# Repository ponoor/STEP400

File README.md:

# STEP400

STEP400 is a 4-axis stepper motor driver board with an Ethernet interface, designed for art installations, stage productions and exhibition machinery. It puts everything a typical motion setup needs onto one board:

- An Arduino Zero–compatible MCU (Microchip ATSAMD21G18A)
- Ethernet (WIZnet W5500)
- Four [STMicroelectronics powerSTEP01](https://www.st.com/en/motor-drivers/powerstep01.html) stepper drivers, supporting both voltage mode and current mode
- HOME and LIMIT sensor inputs for each axis
- A microSD card slot for loading the configuration file

The board is controlled with [Open Sound Control](https://opensoundcontrol.stanford.edu/) (OSC) over Ethernet, which works natively in Max, TouchDesigner, Processing, openFrameworks, Unity and other creative coding environments.

| | |
|---|---|
| Motor type | Bipolar stepper |
| Supply voltage | 12–72 V (absolute max. 80 V) |
| Max. phase current | 5 A |
| Microstepping | Up to 1/128 |
| PCB size | 120 × 84 mm |

STEP400 is part of the STEP series. Its sibling, [STEP800](https://github.com/ponoor/STEP800), drives eight smaller motors with L6470 drivers and shares the same firmware and OSC commands.

Friend of STEP400 : [STEP800](https://github.com/ponoor/STEP800)

## Store
https://ponoor.com/en/shop/

## Documentation
https://ponoor.com/en/docs/step-series/

Forum: https://github.com/ponoor/step-series-support/discussions

- **[STEP400/STEP800 documentation](https://ponoor.com/en/docs/step-series/)** ([日本語](https://ponoor.com/docs/step-series/))
  - [Tutorial](https://ponoor.com/en/docs/step-series/tutorial/)
  - [OSC command reference](https://ponoor.com/en/docs/step-series/osc-command-reference/)
  - [Hardware details](https://ponoor.com/en/docs/step-series/technical-information/hardware-step400/)
- [Electromagnetic brake board for STEP400](https://ponoor.com/en/docs/emb-step400/)
- Questions and support: [STEP series support forum](https://github.com/ponoor/step-series-support/discussions)

## Firmware

The firmware is maintained in a separate repository, shared with STEP800:

**[ponoor/step-series-universal-firmware](https://github.com/ponoor/step-series-universal-firmware)**

This repository used to contain the STEP400 firmware as well. Those directories have been removed, and the old releases here are no longer maintained. See [Firmware update](https://ponoor.com/en/docs/step-series/technical-information/firmware-update/) in the documentation for how to update a board.

## Repository contents

### `hardware/`

Design files for the current hardware revision (r1).

| File | Description |
|---|---|
| `step400_r1.sch`, `step400_r1.brd` | STEP400 r1 schematic and board (Autodesk EAGLE). These are the reference design files for r1. |
| `step400_r1_schematics.pdf` | STEP400 r1 schematic |
| `step400_r1_dimension.pdf` | Board dimensions and mounting holes |
| `step400_r1.0.1_BOM.csv` | Bill of materials for r1.0.1 (current) |
| `step400_r1.0.0_BOM.csv` | Bill of materials for r1.0.0 |
| `brakeBoard.sch`, `brakeBoard.brd` | Electromagnetic brake board (Autodesk EAGLE) |
| `brakeBoard_schematic.pdf`, `brakeBoard_BOM.csv` | Brake board schematic and bill of materials |
| `step400_r1/` | KiCad project imported from the EAGLE r1 files (see below) |

#### KiCad migration (work in progress)

We are moving the hardware design from EAGLE to KiCad for the next revision. `hardware/step400_r1/` holds the r1 design imported into KiCad 10, along with a footprint library (`step400_r1.pretty`) exported from the board.

The connectivity and footprints of this KiCad project have been checked against the EAGLE files. However, it is kept as a **reference for future work**, not as manufacturing data. The PCB still carries leftovers from the import (an unconsolidated layer stack, missing keepout areas, default design rules), so use the EAGLE files or the PDFs above if you need the exact r1 design.

### `configTool/`

Source of the web-based configuration tool, which creates the JSON configuration file that the board loads from its microSD card. A hosted version is available at [ponoor.com/tools/step400-config/](https://ponoor.com/tools/step400-config/). For usage, see [Setup with a microSD card](https://ponoor.com/en/docs/step-series/settings/setup-with-a-microsd-card/).

### `step400_hardware_tests/`

A PlatformIO project for the hardware inspection firmware, used to test assembled boards.

## Examples and libraries

| Environment | Repository |
|---|---|
| Max | [ponoor/step-series-example-Max](https://github.com/ponoor/step-series-example-Max) |
| TouchDesigner | [ponoor/step-series-example-TouchDesigner](https://github.com/ponoor/step-series-example-TouchDesigner) (by [@loveandsheep](https://github.com/loveandsheep)) |
| openFrameworks | [ponoor/step-series-example-openFrameworks](https://github.com/ponoor/step-series-example-openFrameworks) (by [@niimi](https://github.com/niimi)) |
| Unity | [ponoor/step-series-example-Unity](https://github.com/ponoor/step-series-example-Unity) (by [@niimi](https://github.com/niimi)) |
| Processing | [yuskegoto/STEP400_Processing](https://github.com/yuskegoto/STEP400_Processing) (by [@yuskegoto](https://github.com/yuskegoto)) |
| Node-RED | [yuskegoto/STEP400_Node-RED](https://github.com/yuskegoto/STEP400_Node-RED) (by [@yuskegoto](https://github.com/yuskegoto)) |
| Python | [ponoor/python-step-series](https://github.com/ponoor/python-step-series) |

## License

[MIT License](LICENSE) © Ponoor Experiments Inc.

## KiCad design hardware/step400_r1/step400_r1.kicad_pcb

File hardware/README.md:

# Diagram
```mermaid
flowchart LR
	MCU ---|SPI/SERCOM4| W5500 --- Ethernet
	MCU --- |SPI/SERCOM3|PowerSTEP01 --> Motor
	HomeSw -->|SW| PowerSTEP01
	LimitSw -->|ADCIN| PowerSTEP01
	DIPSW --> MCU
	MCU --> Brake
  ```
  
  Check the [document](https://ponoor.com/en/docs/step-series/technical-information/hardware-step400/) for details.

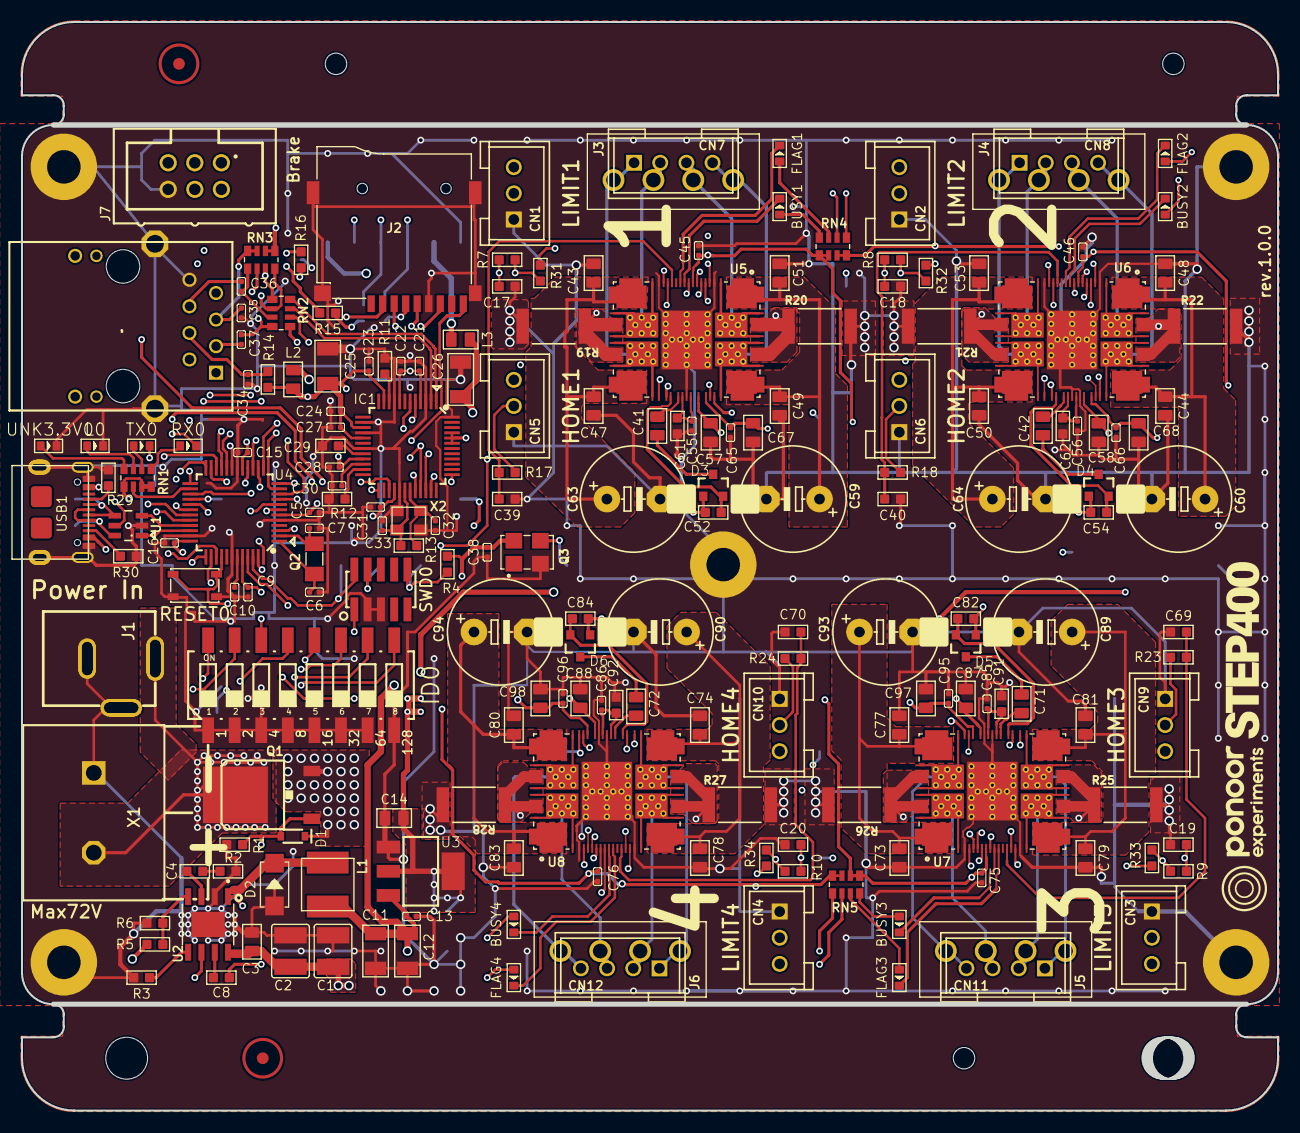
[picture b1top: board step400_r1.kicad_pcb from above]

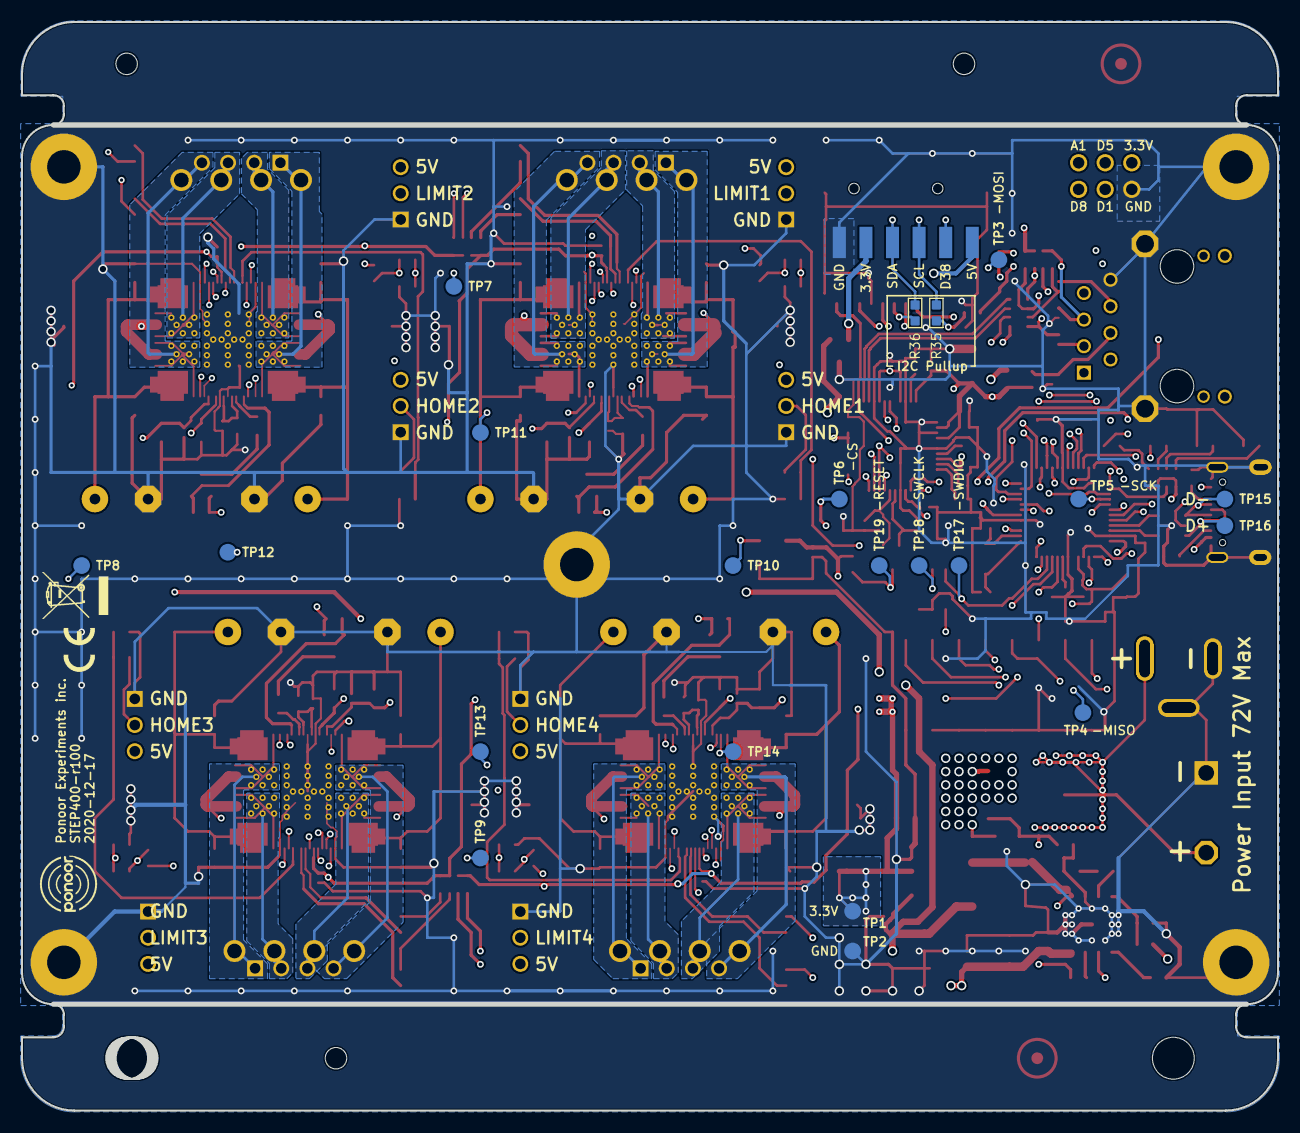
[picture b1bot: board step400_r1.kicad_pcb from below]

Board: 4 copper layers, 120.0 x 104.0 mm, 245 parts (25 on the bottom side), 166 nets.

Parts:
BUSY1, BUSY2, BUSY3, BUSY4: GREEN-0603; LED-0603
C1, C2: 4.7uF/100V; C1210
C3, C57, C58, C87, C88: 100nF/100V; C0805
C4, C8: 100nf; C0603
C5, C9, C10, C13, C15, C16, C21, C22, C23, C24, C27, C28, C31, C38, C45, C46, C55, C56, C75, C76, C85, C86: 100nf; C0402
C6, C7, C32, C33: 22pF; C0402
C11, C12: 47uF; C1206
C14: 10uF/10V; C0805
C17, C18, C19, C20, C39, C40, C69, C70: 1uf; C0603
C25, C26: 47uF/6.3V; C1206
C29: 4.7uF/6.3V; C0603
C30, C35: 10nf; C0402
C34: 22NF 50V; C0402
C36, C37: 6.8nF; C0402
C41, C42, C71, C72: 47nF; C0805
C43, C44, C47, C48, C49, C50, C51, C53, C73, C74, C77, C78, C79, C80, C81, C83: 220nF; C0805
C52, C54, C61, C62, C82, C84, C91, C92: 470nF; C0603
C59, C60, C63, C64, C89, C90, C93, C94: 100uF; E5-10,5
C65, C66, C95, C96: 220nF; C0402
C67, C68, C97, C98: 22uf; C0805
CN1, CN2, CN3, CN4, CN5, CN6, CN9, CN10: B3B-XASK-1
CN7, CN8, CN11, CN12: B4B-XASK-1
D1: 5.1V; SOD-323
D2: 100V 2A; DO-214AC
D3, D4, D5, D6: BAR43; SOT23-3
FLAG1, FLAG2, FLAG3, FLAG4: YELLOW-0603; LED-0603
IC1: 0982_W5500LONG; TQFP48-LONG
ID0: 219-08; CTS-219-08
J1: POWERJACK; POWERJACK_SLOT
J2: SDCARD_SLOT_TF-115K; TF-115K
J3, J4, J5, J6: 691321300004
J7: 61200621621
J8: CONN_06_SMD_FEMALE; 1X06-SMD-FEMALE
L0: BLUE-0603; LED-0603
L1: 150uH; L5045_L
L2, L3: 330R-1500MA; L0805
Q1: SUD50P08-25L-E3; D-PAK_TO252AA
Q2: 32.768kHz; FC-135
Q3: 16MHz; SG5032
R1: 100k; R0603
R2: 4.7k; R0603
R3: 13k; R0603
R4, R12, R31, R32, R33, R34: 10K 1/10W; R0603
R5: 3k; R0603
R6: 750; R0603
R7, R8, R9, R10, R17, R18, R23, R24: 100R; R0603
R11: 12.4K; R0603
R13: 1M 1/10W; R0603
R14: 10R; R0603
R15, R16: 330R; R0603
R19, R20, R21, R22, R25, R26, R27, R28: 0.1; RESC6332X71N
R29, R30: 5.1k; R0603
R35, R36: 4.7K; R0603
RESET0: SWITCH-SPST-2; SKRP
RN1, RN4, RN5: 330; CAY16_LONG_W
RN2: 33; CAY16_LONG_W
RN3: 49.9; CAY16_LONG_W
RX0: RED-0603; LED-0603
S2, S3, S4, S5, S6: STANDOFF_ELECTRICAL; STANDOFF-ELECTRICAL
SWD0: CORTEX_DEBUG_SMT; 20021121-00010C4LF
TP1, TP2, TP3, TP4, TP5, TP6, TP7, TP8, TP9, TP10, TP11, TP12, TP13, TP14, TP15, TP16, TP17, TP18, TP19: TESTPOINT_D1.6
TX0: YELLOW-0603; LED-0603
U1: USBLC6-2SC6; SOT23-6L
U2: BD9G341AEFJ; SOIC127P600X100-9N
U3: LD1117S33; SOT223
U4: ATSAMD21G-A; TQFP-48
U5, U6, U7, U8: POWERSTEP01_VIA; IC_POWERSTEP01_VIA
U$1: STEP400_LOGO_6MM
U$2, U$3: FIDUCIAL_MARKER_PBAN
U$4: PONOOR_LOGO_6MM
U$6: WEEE_6MM
U$8: CE_3MM
UNK3.3V0: GREEN-0603; LED-0603
UNK_HOLE_0: dummyfp0
UNK_HOLE_1: dummyfp1
UNK_HOLE_2: dummyfp2
UNK_HOLE_3: dummyfp3
UNK_HOLE_4: dummyfp4
UNK_HOLE_5: dummyfp5
UNK_HOLE_6: dummyfp6
UNK_HOLE_7: dummyfp7
UNK_HOLE_8: dummyfp8
UNK_HOLE_9: dummyfp9
UNK_HOLE_10: dummyfp10
UNK_HOLE_11: dummyfp11
UNK_HOLE_12: dummyfp12
UNK_HOLE_13: dummyfp13
UNK_HOLE_14: dummyfp14
UNK_HOLE_15: dummyfp15
USB1: USB-C_USB2.0-TYPE-C
X1: CONN_02; WJ25C-B-7.62-2P
X2: 25MHz; CRYSTAL-3.2-2.5
X3: RJ45_MAGNETICS_LED_HR871181A; HR871181A

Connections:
1V2O: C30.2, IC1.22
3.3V: C5.1, C9.1, C14.2, C15.1, C16.1, C38.2, J2.4, J7.5, J8.2, L2.1, L3.1, Q3.4, R4.2, R15.2, R16.2, R35.2, R36.2, RN1.5, RN1.7, RN1.8, SWD0.P$1, TP1.1, U3.2, U3.4, U4.6, U4.17, U4.36, U4.44
5V: C11.2, C12.2, C13.1, CN1.3, CN2.3, CN3.3, CN4.3, CN5.3, CN6.3, CN9.3, CN10.3, J8.6, L1.P$2, R5.2, U1.5, U3.3, USB1.A4_B9, USB1.B4_A9
+3V3A: C21.1, C22.1, C23.1, C24.1, C25.1, C27.1, C28.1, IC1.4, IC1.8, IC1.11, IC1.15, IC1.17, IC1.21, L2.2, R14.2, RN3.1, RN3.2
+3V3D: C26.1, C31.2, IC1.28, IC1.43, IC1.44, IC1.45, L3.2
ACT: IC1.27, X3.12
D13: RN1.6, U4.26
D38: J8.5, U4.22
D+: TP16.1, U1.6, USB1.A6, USB1.B6
D-: TP15.1, U1.4, USB1.A7, USB1.B7
DIPSW1: ID0.16, U4.30
DIPSW2: ID0.15, U4.37
DIPSW3: ID0.14, U4.47
DIPSW4: ID0.13, U4.38
DIPSW5: ID0.12, U4.23
DIPSW6: ID0.11, U4.12
DIPSW7: ID0.10, U4.14
DIPSW8: ID0.9, U4.16
EM_1: J7.1, U4.7
EM_2: J7.2, U4.11
EM_3: J7.3, U4.24
EM_4: J7.4, U4.15
GND: C1.2, C2.2, C3.1, C5.2, C6.1, C7.2, C9.2, C10.2, C11.1, C12.1, C13.2, C14.1, C15.2, C16.2, C17.1, C18.1, C19.1, C20.1, C21.2, C22.2, C23.2, C24.2, C25.2, C26.2, C27.2, C28.2, C29.1, C30.1, C31.1, C32.2, C33.2, C34.2, C35.2, C38.1, C39.1, C40.1, C43.1, C44.1, C45.2, C46.2, C47.1, C48.1, C49.1, C50.1, C51.1, C53.1, C55.2, C56.2, C57.1, C58.1, C59.-, C60.-, C61.1, C62.1, C63.-, C64.-, C65.1, C66.1, C67.1, C68.1, C69.1, C70.1, C73.1, C74.1, C75.2, C76.2, C77.1, C78.1, C79.1, C80.1, C81.1, C83.1, C85.2, C86.2, C87.1, C88.1, C89.-, C90.-, C91.1, C92.1, C93.-, C94.-, C95.1, C96.1, C97.1, C98.1, CN1.1, CN2.1, CN3.1, CN4.1, CN5.1, CN6.1, CN9.1, CN10.1, D2.1, IC1.3, IC1.9, IC1.14, IC1.16, IC1.19, IC1.29, IC1.48, ID0.1, ID0.2, ID0.3, ID0.4, ID0.5, ID0.6, ID0.7, ID0.8, J1.P$33, J1.P$34, J1.P$35, J1.P$36, J1.P$37, J1.P$38, J1.P$39, J1.P$40, J1.P$41, J1.P$42, J1.P$43, J1.P$44, J1.P$45, J1.P$46, J1.P$47, J1.P$48, J1.P$49, J1.P$50, J1.P$51, J1.P$52, J1.P$53, J1.P$54, J1.P$55, J1.P$56, J1.P$63, J1.P$64, J1.P$65, J1.P$66, J1.P$67, J1.P$68, J1.P$69, J1.P$70, J1.P$71, J1.P$72, J1.P$73, J1.P$74, J1.P$75, J1.P$76, J1.P$77, J1.P$78, J1.P$79, J1.P$80, J1.P$81, J1.P$82, J1.P$83, J1.P$84, J1.P$85, J2.6, J2.SHIELD1, J2.SHIELD2, J2.SHIELD3, J2.SHIELD4, J7.6, J8.1, L0.-, Q3.2, R1.1, R2.1, R3.1, R6.1, R11.1, R12.1, R19.2, R20.2, R21.2, R22.2, R25.2, R26.2, R27.2, R28.2, R29.1, R30.2, RESET0.P$3, RESET0.P$4, S2.P1, S3.P1, S4.P1, S5.P1, S6.P1, SWD0.P$3, SWD0.P$5, TP2.1, U1.2, U2.2, U2.9, U3.1, U4.5, U4.18, U4.35, U4.42, U5.8, U5.21, U5.59, U5.EPAD9, U5.EPAD9_VIA1, U5.EPAD9_VIA2, U5.EPAD9_VIA3, U5.EPAD9_VIA4, U5.EPAD9_VIA5, U5.EPAD9_VIA6, U5.EPAD9_VIA7, U5.EPAD9_VIA8, U5.EPAD9_VIA9, U5.EPAD9_VIA10, U5.EPAD9_VIA11, U5.EPAD9_VIA12, U5.EPAD9_VIA13, U5.EPAD9_VIA14, U5.EPAD9_VIA15, U5.EPAD9_VIA16, U5.EPAD9_VIA17, U5.EPAD9_VIA18, U5.EPAD9_VIA19, U5.EPAD9_VIA20, U5.EPAD9_VIA21, U5.EPAD9_VIA22, U6.8, U6.21, U6.59, U6.EPAD9, U6.EPAD9_VIA1, U6.EPAD9_VIA2, U6.EPAD9_VIA3, U6.EPAD9_VIA4, U6.EPAD9_VIA5, U6.EPAD9_VIA6, U6.EPAD9_VIA7, U6.EPAD9_VIA8, U6.EPAD9_VIA9, U6.EPAD9_VIA10, U6.EPAD9_VIA11, U6.EPAD9_VIA12, U6.EPAD9_VIA13, U6.EPAD9_VIA14, U6.EPAD9_VIA15, U6.EPAD9_VIA16, U6.EPAD9_VIA17, U6.EPAD9_VIA18, U6.EPAD9_VIA19, U6.EPAD9_VIA20, U6.EPAD9_VIA21, U6.EPAD9_VIA22, U7.8, U7.21, U7.59, U7.EPAD9, U7.EPAD9_VIA1, U7.EPAD9_VIA2, U7.EPAD9_VIA3, U7.EPAD9_VIA4, U7.EPAD9_VIA5, U7.EPAD9_VIA6, U7.EPAD9_VIA7, U7.EPAD9_VIA8, U7.EPAD9_VIA9, U7.EPAD9_VIA10, U7.EPAD9_VIA11, U7.EPAD9_VIA12, U7.EPAD9_VIA13, U7.EPAD9_VIA14, U7.EPAD9_VIA15, U7.EPAD9_VIA16, U7.EPAD9_VIA17, U7.EPAD9_VIA18, U7.EPAD9_VIA19, U7.EPAD9_VIA20, U7.EPAD9_VIA21, U7.EPAD9_VIA22, U8.8, U8.21, U8.59, U8.EPAD9, U8.EPAD9_VIA1, U8.EPAD9_VIA2, U8.EPAD9_VIA3, U8.EPAD9_VIA4, U8.EPAD9_VIA5, U8.EPAD9_VIA6, U8.EPAD9_VIA7, U8.EPAD9_VIA8, U8.EPAD9_VIA9, U8.EPAD9_VIA10, U8.EPAD9_VIA11, U8.EPAD9_VIA12, U8.EPAD9_VIA13, U8.EPAD9_VIA14, U8.EPAD9_VIA15, U8.EPAD9_VIA16, U8.EPAD9_VIA17, U8.EPAD9_VIA18, U8.EPAD9_VIA19, U8.EPAD9_VIA20, U8.EPAD9_VIA21, U8.EPAD9_VIA22, UNK3.3V0.-, USB1.A1_B12, USB1.B1_A12, USB1.S7, USB1.S8, USB1.S9, USB1.S10, USB1.S11, USB1.S12, USB1.S13, USB1.S14, USB1.S15, USB1.S16, USB1.S17, USB1.S18, USB1.S19, USB1.S20, USB1.S21, USB1.S22, USB1.S23, USB1.S24, USB1.S25, USB1.S26, USB1.S27, USB1.S29, USB1.S30, USB1.S31, USB1.S32, USB1.S33, USB1.S34, USB1.S35, USB1.S36, USB1.S37, USB1.S38, USB1.S39, USB1.S40, USB1.S41, USB1.S42, USB1.S43, USB1.S44, USB1.S45, USB1.S46, USB1.S47, USB1.S48, X1.P$1, X2.2, X2.4, X3.8, X3.SHIELD1, X3.SHIELD2
LIMIT1: C17.2, R7.2, U5.54
LIMIT2: C18.2, R8.2, U6.54
LIMIT3: C19.2, R9.2, U7.54
LIMIT4: C20.2, R10.2, U8.54
LINKLED: IC1.25, X3.10
unnamed: TP14.1, U8.64
unnamed: C6.2, Q2.P$2, U4.1
unnamed: C4.1, R2.2
unnamed: C7.1, Q2.P$1, U4.2
unnamed: RN1.1, RX0.+
unnamed: RN1.2, TX0.+
unnamed: R5.1, R6.2, U2.4
unnamed: D1.A, Q1.1, R1.2, U2.6
unnamed: R3.2, U2.5
unnamed: L0.+, RN1.3
unnamed: RN1.4, UNK3.3V0.+
unnamed: C4.2, U2.3
unnamed: C32.1, IC1.31, R13.1, X2.3
unnamed: CN1.2, R7.1, R31.1
unnamed: C8.1, U2.7
unnamed: CN2.2, R8.1, R32.1
unnamed: C8.2, D2.2, L1.P$1, U2.1
unnamed: BUSY1.+, RN4.8
unnamed: C34.1, R14.1, X3.4
unnamed: CN5.2, R17.1
unnamed: C35.1, RN3.3, RN3.4, X3.5
unnamed: R15.1, X3.9
unnamed: R16.1, X3.11
unnamed: IC1.23, R12.2
unnamed: C39.2, R17.2, U5.18
unnamed: C40.2, R18.2, U6.18
unnamed: CN6.2, R18.1
unnamed: C69.2, R23.2, U7.18
unnamed: CN9.2, R23.1
unnamed: FLAG1.+, RN4.7
unnamed: C70.2, R24.2, U8.18
unnamed: C41.2, D3.3
unnamed: C41.1, U5.57
unnamed: CN10.2, R24.1
unnamed: CN3.2, R9.1, R33.1
unnamed: BUSY2.+, RN4.6
unnamed: FLAG2.+, RN4.5
unnamed: C29.2, IC1.20
unnamed: FLAG1.-, U5.16
unnamed: IC1.10, R11.2
unnamed: BUSY1.-, U5.15
unnamed: R20.1, U5.9, U5.77, U5.82
unnamed: R19.1, U5.20, U5.34, U5.39
unnamed: CN4.2, R10.1, R34.1
unnamed: R30.1, USB1.B5
unnamed: CN7.1, J3.1, U5.38, U5.42, U5.53, U5.EPAD4, U5.EPAD4_VIA1, U5.EPAD4_VIA2, U5.EPAD4_VIA3, U5.EPAD4_VIA4, U5.EPAD4_VIA5, U5.EPAD4_VIA6, U5.EPAD4_VIA7, U5.EPAD4_VIA8
unnamed: CN7.2, J3.2, U5.22, U5.33, U5.37, U5.EPAD3, U5.EPAD3_VIA1, U5.EPAD3_VIA2, U5.EPAD3_VIA3, U5.EPAD3_VIA4, U5.EPAD3_VIA5, U5.EPAD3_VIA6, U5.EPAD3_VIA7, U5.EPAD3_VIA8
unnamed: TP7.1, U5.14, U6.12
unnamed: R29.2, USB1.A5
unnamed: CN7.3, J3.3, U5.7, U5.81, U5.85, U5.EPAD8, U5.EPAD8_VIA1, U5.EPAD8_VIA2, U5.EPAD8_VIA3, U5.EPAD8_VIA4, U5.EPAD8_VIA5, U5.EPAD8_VIA6, U5.EPAD8_VIA7, U5.EPAD8_VIA8
unnamed: CN7.4, J3.4, U5.65, U5.76, U5.80, U5.EPAD7, U5.EPAD7_VIA1, U5.EPAD7_VIA2, U5.EPAD7_VIA3, U5.EPAD7_VIA4, U5.EPAD7_VIA5, U5.EPAD7_VIA6, U5.EPAD7_VIA7, U5.EPAD7_VIA8
unnamed: C42.2, D4.3
unnamed: C42.1, U6.57
unnamed: BUSY3.+, RN5.8
unnamed: FLAG3.+, RN5.7
unnamed: FLAG2.-, U6.16
unnamed: BUSY2.-, U6.15
unnamed: R22.1, U6.9, U6.77, U6.82
unnamed: R21.1, U6.20, U6.34, U6.39
unnamed: TP12.1, U6.64, U7.63
unnamed: CN8.1, J4.1, U6.38, U6.42, U6.53, U6.EPAD4, U6.EPAD4_VIA1, U6.EPAD4_VIA2, U6.EPAD4_VIA3, U6.EPAD4_VIA4, U6.EPAD4_VIA5, U6.EPAD4_VIA6, U6.EPAD4_VIA7, U6.EPAD4_VIA8
unnamed: CN8.2, J4.2, U6.22, U6.33, U6.37, U6.EPAD3, U6.EPAD3_VIA1, U6.EPAD3_VIA2, U6.EPAD3_VIA3, U6.EPAD3_VIA4, U6.EPAD3_VIA5, U6.EPAD3_VIA6, U6.EPAD3_VIA7, U6.EPAD3_VIA8
unnamed: CN8.3, J4.3, U6.7, U6.81, U6.85, U6.EPAD8, U6.EPAD8_VIA1, U6.EPAD8_VIA2, U6.EPAD8_VIA3, U6.EPAD8_VIA4, U6.EPAD8_VIA5, U6.EPAD8_VIA6, U6.EPAD8_VIA7, U6.EPAD8_VIA8
unnamed: CN8.4, J4.4, U6.65, U6.76, U6.80, U6.EPAD7, U6.EPAD7_VIA1, U6.EPAD7_VIA2, U6.EPAD7_VIA3, U6.EPAD7_VIA4, U6.EPAD7_VIA5, U6.EPAD7_VIA6, U6.EPAD7_VIA7, U6.EPAD7_VIA8
unnamed: BUSY4.+, RN5.6
unnamed: C82.1, D5.2, U7.56
unnamed: C71.2, D5.3
unnamed: C71.1, U7.57
unnamed: FLAG4.+, RN5.5
unnamed: CN11.4, J5.4, U7.65, U7.76, U7.80, U7.EPAD7, U7.EPAD7_VIA1, U7.EPAD7_VIA2, U7.EPAD7_VIA3, U7.EPAD7_VIA4, U7.EPAD7_VIA5, U7.EPAD7_VIA6, U7.EPAD7_VIA7, U7.EPAD7_VIA8
unnamed: FLAG3.-, U7.16
unnamed: BUSY3.-, U7.15
unnamed: R26.1, U7.9, U7.77, U7.82
unnamed: R25.1, U7.20, U7.34, U7.39
unnamed: TP8.1, U6.14, U7.12
unnamed: CN11.1, J5.1, U7.38, U7.42, U7.53, U7.EPAD4, U7.EPAD4_VIA1, U7.EPAD4_VIA2, U7.EPAD4_VIA3, U7.EPAD4_VIA4, U7.EPAD4_VIA5, U7.EPAD4_VIA6, U7.EPAD4_VIA7, U7.EPAD4_VIA8
unnamed: CN11.2, J5.2, U7.22, U7.33, U7.37, U7.EPAD3, U7.EPAD3_VIA1, U7.EPAD3_VIA2, U7.EPAD3_VIA3, U7.EPAD3_VIA4, U7.EPAD3_VIA5, U7.EPAD3_VIA6, U7.EPAD3_VIA7, U7.EPAD3_VIA8
unnamed: CN11.3, J5.3, U7.7, U7.81, U7.85, U7.EPAD8, U7.EPAD8_VIA1, U7.EPAD8_VIA2, U7.EPAD8_VIA3, U7.EPAD8_VIA4, U7.EPAD8_VIA5, U7.EPAD8_VIA6, U7.EPAD8_VIA7, U7.EPAD8_VIA8
unnamed: CN12.4, J6.4, U8.65, U8.76, U8.80, U8.EPAD7, U8.EPAD7_VIA1, U8.EPAD7_VIA2, U8.EPAD7_VIA3, U8.EPAD7_VIA4, U8.EPAD7_VIA5, U8.EPAD7_VIA6, U8.EPAD7_VIA7, U8.EPAD7_VIA8
unnamed: CN12.3, J6.3, U8.7, U8.81, U8.85, U8.EPAD8, U8.EPAD8_VIA1, U8.EPAD8_VIA2, U8.EPAD8_VIA3, U8.EPAD8_VIA4, U8.EPAD8_VIA5, U8.EPAD8_VIA6, U8.EPAD8_VIA7, U8.EPAD8_VIA8
unnamed: C84.1, D6.2, U8.56
unnamed: C72.2, D6.3
unnamed: C72.1, U8.57
unnamed: FLAG4.-, U8.16
unnamed: BUSY4.-, U8.15
unnamed: R28.1, U8.9, U8.77, U8.82
unnamed: R27.1, U8.20, U8.34, U8.39
unnamed: CN12.1, J6.1, U8.38, U8.42, U8.53, U8.EPAD4, U8.EPAD4_VIA1, U8.EPAD4_VIA2, U8.EPAD4_VIA3, U8.EPAD4_VIA4, U8.EPAD4_VIA5, U8.EPAD4_VIA6, U8.EPAD4_VIA7, U8.EPAD4_VIA8
unnamed: CN12.2, J6.2, U8.22, U8.33, U8.37, U8.EPAD3, U8.EPAD3_VIA1, U8.EPAD3_VIA2, U8.EPAD3_VIA3, U8.EPAD3_VIA4, U8.EPAD3_VIA5, U8.EPAD3_VIA6, U8.EPAD3_VIA7, U8.EPAD3_VIA8
unnamed: Q3.3, TP10.1, U5.63
unnamed: TP11.1, U5.64, U6.63
unnamed: TP13.1, U7.64, U8.63
unnamed: TP9.1, U7.14, U8.12
OSC2E2: C33.1, IC1.30, R13.2, X2.1
POWERSTEP_CS: TP6.1, U4.3, U5.10, U6.10, U7.10, U8.10
POWERSTEP_MISO: TP4.1, U4.29, U8.14
POWERSTEP_MOSI: TP3.1, U4.25, U5.12
POWERSTEP_RESET: U4.8, U5.19, U6.19, U7.19, U8.19
POWERSTEP_SCK: TP5.1, U4.28, U5.11, U6.11, U7.11, U8.11
RDN: C36.2, X3.6
RDP: C37.2, X3.3
RXI_N: C36.1, RN2.3, RN3.5
RXI_P: C37.1, RN2.4, RN3.6
RX_LED: RX0.-, U4.48
RX_N: IC1.5, RN2.6
RX_P: IC1.6, RN2.5
SCL: J8.4, R35.1, U4.32
SDA: J8.3, R36.1, U4.31
SD_CS: J2.2, U4.13
SD_DETECT: J2.CD, U4.10
SPI_MISO: IC1.34, J2.7, U4.21
SPI_MOSI: IC1.35, J2.3, U4.19
SPI_SCK: IC1.33, J2.5, U4.20
SWCLK: SWD0.P$4, TP18.1, U4.45
SWDIO: SWD0.P$2, TP17.1, U4.46
TXO_N: RN2.1, RN3.7, X3.2
TXO_P: RN2.2, RN3.8, X3.1
TX_LED: TX0.-, U4.39
TX_N: IC1.1, RN2.8
TX_P: IC1.2, RN2.7
USB_D_N: U1.3, U4.33
USB_D_P: U1.1, U4.34
VBOOT_1: C52.1, D3.2, U5.56
VBOOT_2: C54.1, D4.2, U6.56
VCC_1: C55.1, C61.2, U5.58, U5.60
VCC_2: C56.1, C62.2, U6.58, U6.60
VCC_3: C85.1, C91.2, U7.58, U7.60
VCC_4: C86.1, C92.2, U8.58, U8.60
VDDCORE: C10.1, U4.43
VDDIO_1: C45.1, C65.2, C67.2, R31.2, RN4.1, RN4.2, U5.13, U5.62
VDDIO_2: C46.1, C66.2, C68.2, R32.2, RN4.3, RN4.4, U6.13, U6.62
VDDIO_3: C75.1, C95.2, C97.2, R33.2, RN5.1, RN5.2, U7.13, U7.62
VDDIO_4: C76.1, C96.2, C98.2, R34.2, RN5.3, RN5.4, U8.13, U8.62
VIN: C1.1, C2.1, C3.2, C43.2, C44.2, C47.2, C48.2, C49.2, C50.2, C51.2, C52.2, C53.2, C54.2, C57.2, C58.2, C59.+, C60.+, C63.+, C64.+, C73.2, C74.2, C77.2, C78.2, C79.2, C80.2, C81.2, C82.2, C83.2, C84.2, C87.2, C88.2, C89.+, C90.+, C93.+, C94.+, D1.C, D3.1, D4.1, D5.1, D6.1, Q1.3, U2.8, U5.1, U5.23, U5.43, U5.55, U5.61, U5.66, U6.1, U6.23, U6.43, U6.55, U6.61, U6.66, U7.1, U7.23, U7.43, U7.55, U7.61, U7.66, U8.1, U8.23, U8.43, U8.55, U8.61, U8.66
VRAW: J1.P$2, J1.P$3, J1.P$4, J1.P$5, J1.P$6, J1.P$7, J1.P$8, J1.P$9, J1.P$10, J1.P$11, J1.P$12, J1.P$13, J1.P$14, J1.P$15, J1.P$16, J1.P$17, J1.P$18, J1.P$19, J1.P$20, J1.P$21, J1.P$22, J1.P$23, J1.P$24, J1.P$25, J1.P$26, J1.P$27, J1.P$28, Q1.4, X1.P$2
W5500_CS: IC1.32, U4.27
W5500_RST: IC1.37, U4.9
~RESET: R4.1, RESET0.P$1, RESET0.P$2, SWD0.P$10, TP19.1, U4.40

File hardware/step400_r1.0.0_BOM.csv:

#,Name,Value,Description,Package,Manufacture,Manufacturer Part Number,Designator,Qty,Type,
1,SMD-LED,GREEN,general LED green,LED-0603,Lite-On,LTST-C193TGKT-5A,"3.3V, BUSY1, BUSY2, BUSY3, BUSY4",5,SMD,
2,MLCC,4.7uF/100V,4.7uF / 20% / 100V / X5R,C1210,Samsung Electro-Mechanics,CL32B475KCVZW6E,"C1, C2",2,SMD,
3,MLCC,47uF/6.3V,47uF / 20% / 6.3V / X5R,C1206,Samsung Electro-Mechanics,CL31A476MQHNNWE,"C11, C12, C25, C26",4,SMD,
4,MLCC,10uF/10V,10uF / 20% / 10V / X5R,C0805,Samsung Electro-Mechanics,CL21A106KOQNNNG,C14,1,SMD,
5,MLCC,1uF/6.3V,1uF / 20% / 6.3V / X5R,C0603,Samsung Electro-Mechanics,CL10A105KO8NNNC,"C17, C18, C19, C20, C39, C40, C69, C70",8,SMD,
6,MLCC,4.7uF/6.3V,4.7uF / 20% / 6.3V / X5R,C0603,Samsung Electro-Mechanics,CL10A475KQ8NNNC,C29,1,SMD,
7,MLCC,100nF/100V,100nF / 20% / 100V / X5R,C0805,Samsung Electro-Mechanics,CL21B104KCFNNNE,"C3, C57, C58, C87, C88",5,SMD,
8,MLCC,10nF/25V,10nF / 20% / 25V / X5R ,C0402,Walsin Tech Corp,0402B103K250,"C30, C35",2,SMD,
9,MLCC,22nF 50V,22nF / 20% / 50V / X5R,C0402,Walsin Tech Corp,0402F223Z500CT,C34,1,SMD,
10,MLCC,6.8nF/25V,6.8nF / 20% / 25V / X5R ,C0402,Walsin Tech Corp,0402B682K500CT,"C36, C37",2,SMD,
11,MLCC,100nF/50V,100nF / 20% / 50V / X5R,C0603,Walsin Tech Corp,0603B104K500CT,"C4, C8",2,SMD,
12,MLCC,47nF/50V,47nF / 20% / 50V / X5R,C0805,Samsung Electro-Mechanics,CL21F473ZBANNNC,"C41, C42, C71, C72",4,SMD,
13,MLCC,220nF/100V,220nF / 20% / 100V / X5R,C0805,Samsung Electro-Mechanics,CL21B224KCFSFNE,"C43, C44, C47, C48, C49, C50, C51, C53, C73, C74, C77, C78, C79, C80, C81, C83",16,SMD,
14,MLCC,100nF / 25V,100nF / 20% / 25V / X5R,C0402,Walsin Tech Corp,0402X104K160CT,"C5, C9, C10, C13, C15, C16, C21, C22, C23, C24, C27, C28, C31, C38, C45, C46, C55, C56, C75, C76, C85, C86",22,SMD,
15,MLCC,470nF/25V,470nF / 20% / 25V / X5R ,C0603,Samsung Electro-Mechanics,CL10B474KA8NNNC,"C52, C54, C61, C62, C82, C84, C91, C92",8,SMD,
16,Chemical Capacitor,100uF/100V,100uF / 20% / 100V,"E5-10,5",Rubycon,100PX100MEFC10X16,"C59, C60, C63, C64, C89, C90, C93, C94",8,THT,
17,MLCC,22pF/50V,22pF / 10% / 50V / X5R,C0402,Walsin Tech Corp,0402N220J500,"C6, C7, C32, C33",4,SMD,
18,MLCC,220nF/6.3V,220nF / 20% / 6.3V / X5R,C0402,Walsin Tech Corp,0402X224K6R3CT,"C65, C66, C95, C96",4,SMD,
19,MLCC,22uF/6.3V,22uF / 20% / 6.3V / X5R,C0805,Samsung Electro-Mechanics,CL21A226MQQNNNE,"C67, C68, C97, C98",4,SMD,
20,Shrouded header,"2.5mm, 3P",B3B-XASK-1,B3B-XASK-1,JST,B03B-XASK-1(LF)(SN),"CN1, CN2, CN3, CN4, CN5, CN6, CN9, CN10",8,THT,
21,Shrouded header,"2.5mm, 4P",B4B-XASK-1,B4B-XASK-1,JST,B04B-XASK-1(LF)(SN),"CN7, CN8, CN11, CN12",4,THT,NO mount
22,Zener Diode,"5.6V, 300mW",5.6V ±7% 300mW ,SOD-323,ON Semiconductor,MM3Z5V6T1G,D1,1,SMD,
23,Schottky diode,100V 2A,"100V, 2A",DO-214AC,Guangdong Hottech,SS210A,D2,1,SMD,
24,Switching diode array,BAR43,"30V, 100mA",SOT23-3,STMicroelectronics,BAR43SFILM,"D3, D4, D5, D6",4,SMD,
25,SMD-LED,Red,general LED red,LED-0603,Lite-On,LTST-C193KRKT-5A,"FLAG1, FLAG2, FLAG3, FLAG4, TX",5,SMD,
26,Ethernet Controller,,,TQFP48,WIZnet,W5500,IC1,1,SMD,
27,DIP Switch,,8 digits,2.54mm pitch SMD,Cixi Tonver Elec,HAD-08HWA-R,ID,1,SMD,
28,DC Power receptacle,,DC Power Receptacle Jack 5A 2.0mm 6.2mm,POWERJACK_SLOT,XKB Connectivity,DC-005-5A-2.0,J1,1,SMD,
29,Micro SD card slot,,,,XUNPU,TF-115K,J2,1,SMD,
30,3.81mm 4pin header,,,,Ningbo Kangnex Elec,WJ15EDGVC-3.81-4P,"J3, J4, J5, J6",4,THT,
31,Box header,,"Header 6P 0.100""(2.54mm) 2",61200621621,Ckmtw(Shenzhen Cankemeng),C132438,J7,1,THT,
32,SMD-LED,Orange,general LED orange,LED-0603,Lite-On,LTST-C191KFKT,L,1,SMD,
33,Power Inductor,15uH,±20% 1.9A,L5050,TDK,VLS5045EX-150M,L1,1,SMD,
34,Ferrite Beads,330R-1500MA,330Ω @ 100MHz 1.5A,L0805,Murata Electronics,"BLM21PG331SN1D","L2, L3",2,SMD,
35,P-MOSFET,,100V 46A,D-PAK(TO252AA),Winsok Semicon,WSF45P10,Q1,1,SMD,
36,Crystal Resonators,32.768kHz,CRYSTAL,SMD-3215_2P,EPSON,FC-135 32.7680KA-A0,Q2,1,SMD,
37,Crystal Oscillator,,16MHz ±100ppm 3.3V,SG5032,Seiko Epson,X1G004451000200,Q3,1,SMD,
38,Chip Resistor,100k,5% 1/10W,R0603,YAGEO,RC0603JR-07100KL,R1,1,SMD,
39,Chip Resistor,12.4K,1％ 1/10W,R0603,YAGEO,AC0603FR-0712K4L,R11,1,SMD,
40,Chip Resistor,1M 1/10W,5% 1/10W,R0603,YAGEO,AC0603JR-071ML,R13,1,SMD,
41,Chip Resistor,10R,5% 1/10W,R0603,YAGEO,RC0603JR-0710RL,R14,1,SMD,
42,Chip Resistor,330R,5% 1/10W,R0603,YAGEO,RC0603JR-07330RL,"R15, R16",2,SMD,
43,Chip Resistor,0.1,1% 3W,R2512,Bourns,CRA2512-FZ-R100ELF,"R19, R20, R21, R22, R25, R26, R27, R28",8,SMD,
44,Chip Resistor,4.7k,5% 1/10W,R0603,YAGEO,AC0603JR-074K7L,R2,1,SMD,
45,Chip Resistor,5.1k,±0.5% 0.1W,R0603,YAGEO,RC0603DR-075K1L,"R29, R30",2,SMD,
46,Chip Resistor,13k,1％ 1/10W,R0603,YAGEO,RC0603FR-0713KL,R3,1,SMD,
47,Chip Resistor,10K 1/10W,5% 1/10W,R0603,YAGEO,RC0603JR-0710KL,"R4, R12, R31, R32, R33, R34",6,SMD,
48,Chip Resistor,3k,1％ 1/10W,R0603,YAGEO,RC0603FR-073KL,R5,1,SMD,
49,Chip Resistor,750,1％ 1/10W,R0603,YAGEO,AC0603DR-07750RL,R6,1,SMD,
50,Chip Resistor,100R,5% 1/10W,R0603,YAGEO,RC0603JR-07100RL,"R7, R8, R9, R10, R17, R18, R23, R24",8,SMD,
51,Tactile Switch,,SWITCH-SPST,4.6x3.2,ALPS Electric,SKRPABE010,RESET,1,SMD,
52,Array Chip Resistor,330,5% 1/16W,R0603 x4,Bourns,CAY16-331J4LF,"RN1, RN4, RN5",3,SMD,
53,Array Chip Resistor,33,5% 1/16W,R0603 x4,Bourns,CAY16-330J4LF,RN2,1,SMD,
54,Array Chip Resistor,49.9,1% 1/16W,R0603 x4,Bourns,CAY16-49R9F4LF,RN3,1,SMD,
55,SMD-LED,Yellow,general LED yellow,LED-0603,Lite-On,LTST-C191KSKT,RX,1,SMD,
56,Pin Header,10 pin,Cortex Debug Connector,1.27mm Pin Header 10P,Amphenol ICC,20021121-00010C4LF,SWD,1,SMD,
57,TVS Diode Array,USBLC6-2SC6,STMicroelectronics  USBLC6,SOT23-6L,STMicroelectronics,USBLC6-2SC6,U1,1,SMD,
58,DC-DC converter,,,HTSOP-J8,ROHM,BD9G341AEFJ-E2,U2,1,SMD,
59,Voltage Regulator,LD1117S33,3.3V 0.8A,SOT223,STMicroelectronics,LD1117S33TR,U3,1,SMD,
60,MCU,,,TQFP-48,Microchip,ATSAMD21G18A-AU,U4,1,SMD,
61,Stepper Motor Driver,,,VFQFPN89,STMicroelectronics,POWERSTEP01TR,"U5, U6, U7, U8",4,SMD,
62,USB Type C Connector,,USB - Type C Female 16 SMT,USB-C_USB2.0-TYPE-C,XKB Connectivity,U262-161N-4BVC11,USB1,1,THT,
63,Barrier Terminal Block,"7.62mm, 2P",,7.62mm,Ningbo Kangnex Elec,WJ25C-B-7.62-2P,X1,1,SMD,
64,Crystal Resonators ,25MHz,25MHz ±20ppm12pF,CRYSTAL-3225,Seiko Epson,X1E000021013900,X2,1,SMD,
65,RJ45 Jack with Magnetics,,,,Hanrun,HR871181A,X3,1,THT,

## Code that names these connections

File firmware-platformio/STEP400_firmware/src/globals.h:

// globals.h

#ifndef _GLOBALS_h
#define _GLOBALS_h

#if defined(ARDUINO) && ARDUINO >= 100
	#include "arduino.h"
#else
	#include "WProgram.h"
#endif
#include <SPI.h>
#include <Ponoor_PowerSTEP01Library.h>
#include <Ethernet.h>

//#define PROTOTYPE_R4 // Uncomment this line for the prototype r4 pcb.

// =============================================================================
// Pin definitions
// =============================================================================
#define ledPin	13u

#ifdef PROTOTYPE_R4
const uint8_t dipSwPin[8] = { A5,SCL,7u,SDA,2u,9u,3u,0u }; // Prototype_r4
const uint8_t limitSwPin[4] = { 1u,5u,8u,A1 };
#else
const uint8_t dipSwPin[8] = { 7u,30u,A5,31u,2u,9u,3u,0u };
#endif

#define SD_CS_PIN	4u

const uint8_t brakePin[4] = { A1,8u,5u,1u };
#define SD_DETECT_PIN   A4

#define POWERSTEP_MISO	6u	// D6 /SERCOM3/PAD[2] miso
#define POWERSTEP_MOSI	11u	// D11/SERCOM3/PAD[0] mosi
#define POWERSTEP_SCK	12u	// D12/SERCOM3/PAD[3] sck
#define POWERSTEP_CS_PIN A0
#define POWERSTEP_RESET_PIN A2

#define W5500_RESET_PIN A3

// =============================================================================
// Constants and variables
// =============================================================================

// General
#define COMPILE_DATE __DATE__
#define COMPILE_TIME __TIME__
extern const char *firmwareName;
extern const uint8_t firmwareVersion[3]; // defined in the main Arduino sketch
extern int8_t loadedConfigVersion[2];
extern const uint8_t applicableConfigVersion[2];
#define STATUS_POLL_PERIOD   1 // [ms]


// Tx, Rx LED
extern bool rxLedEnabled, txLedEnabled;
extern uint32_t RXL_blinkStartTime, TXL_blinkStartTime;
#define RXL_TXL_BLINK_DURATION	30 // ms

// Json configuration file
constexpr char* filename = "/config.txt";
extern String configName;
extern String configTargetProduct;
extern bool sdInitializeSucceeded;
extern bool configFileOpenSucceeded;
extern bool configFileParseSucceeded;

// PowerSTEP01
#define NUM_OF_MOTOR   (4)
extern powerSTEP stepper[];
#define MOTOR_ID_ALL    255
#define MOTOR_ID_FIRST  1
#define MOTOR_ID_LAST   4

// Network
extern uint8_t mac[6], mac_from_config[6], myId;
extern IPAddress
    myIp,
    myIp_from_config,
    destIp,
    dns,
    gateway,
    subnet;
const IPAddress broadcastIp(255, 255, 255, 255);
extern unsigned int inPort, outPort, outPort_from_config;
extern EthernetUDP Udp;
extern bool
    isDestIpSet,
    isMyIpAddId,
    isMacAddId,
    isOutPortAddId,
    bootedMsgEnable,
    isWaitingSendBootMsg,
    reportErrors;
#define BOOT_MSG_WAIT_TIME  1000    //[ms], The waiting duration for sending a boot message after Ethernet has been linked

// Motor settings.
#define TVAL_LIMIT_VAL  64 // approx. 5A

// Brake
extern uint8_t brakeStatus[NUM_OF_MOTOR];
enum {
    BRAKE_ENGAGED = 0,
    BRAKE_DISENGAGE_WAITING, // motor excited
    BRAKE_DISENGAGED,
    BRAKE_MOTORHIZ_WAITING // brake closed
};
extern uint32_t brakeTransitionTrigTime[NUM_OF_MOTOR];
extern bool bBrakeDecWaiting[NUM_OF_MOTOR]; // Waiting deceleration for the brake engaging procedure

// Homing
extern uint32_t homingStartTime[NUM_OF_MOTOR];
extern uint8_t homingStatus[NUM_OF_MOTOR];
extern bool bHoming[NUM_OF_MOTOR];
extern float homingSpeed[NUM_OF_MOTOR];
enum {
    HOMING_UNDEFINED = 0,
    HOMING_GOUNTIL,
    HOMING_RELEASESW,
    HOMING_COMPLETED,
    HOMING_TIMEOUT
};

// Command errors
enum {
    ERROR_COMMAND_IGNORED = 0,
    ERROR_MOTORID_NOTMATCH,
    ERROR_BRAKE_ENGAGED,
    ERROR_HOMESW_ACTIVATING,
    ERROR_LIMITSW_ACTIVATING,
    ERROR_GOUNTIL_TIMEOUT,
    ERROR_RELEASESW_TIMEOUT,
    ERROR_IN_SERVO_MODE
};
const String commandErrorText[8] = {
    F("CommandIgnored"),
    F("MotorIdNotMatch"),
    F("BrakeEngaged"),
    F("HomeSwActivating"),
    F("LimitSwActivating"),
    F("GoUntilTimeout"),
    F("ReleaseSwTimeout"),
    F("InServoMode")
};
// These values will be initialized at loadConfig()
extern bool
    busy[NUM_OF_MOTOR],
    HiZ[NUM_OF_MOTOR],
    homeSwState[NUM_OF_MOTOR],
    dir[NUM_OF_MOTOR],
    uvloStatus[NUM_OF_MOTOR];
extern uint8_t
    motorStatus[NUM_OF_MOTOR],
    thermalStatus[NUM_OF_MOTOR];

extern bool
    reportBUSY[NUM_OF_MOTOR],
    reportHiZ[NUM_OF_MOTOR],
    reportHomeSwStatus[NUM_OF_MOTOR],
    reportDir[NUM_OF_MOTOR],
    reportMotorStatus[NUM_OF_MOTOR],
    reportSwEvn[NUM_OF_MOTOR],
    reportUVLO[NUM_OF_MOTOR],
    reportThermalStatus[NUM_OF_MOTOR],
    reportOCD[NUM_OF_MOTOR],
    reportStall[NUM_OF_MOTOR],
    limitSwState[NUM_OF_MOTOR],
    reportLimitSwStatus[NUM_OF_MOTOR],
    limitSwMode[NUM_OF_MOTOR],
    homingDirection[NUM_OF_MOTOR],
    bProhibitMotionOnHomeSw[NUM_OF_MOTOR],
    bProhibitMotionOnLimitSw[NUM_OF_MOTOR],
    bHomingAtStartup[NUM_OF_MOTOR];
extern uint16_t
    goUntilTimeout[NUM_OF_MOTOR],
    releaseSwTimeout[NUM_OF_MOTOR];
extern uint8_t kvalHold[NUM_OF_MOTOR], kvalRun[NUM_OF_MOTOR], kvalAcc[NUM_OF_MOTOR], kvalDec[NUM_OF_MOTOR];
extern uint8_t tvalHold[NUM_OF_MOTOR], tvalRun[NUM_OF_MOTOR], tvalAcc[NUM_OF_MOTOR], tvalDec[NUM_OF_MOTOR];
extern bool isCurrentMode[NUM_OF_MOTOR];
extern bool homeSwMode[NUM_OF_MOTOR];

extern uint16_t intersectSpeed[NUM_OF_MOTOR]; // INT_SPEED
extern uint8_t
    startSlope[NUM_OF_MOTOR], // ST_SLP
    accFinalSlope[NUM_OF_MOTOR], // FN_SLP_ACC
    decFinalSlope[NUM_OF_MOTOR], // FN_SLP_DEC
    stallThreshold[NUM_OF_MOTOR]; // STALL_TH
extern uint8_t
    fastDecaySetting[NUM_OF_MOTOR], // T_FAST
    minOnTime[NUM_OF_MOTOR], // TON_MIN
    minOffTime[NUM_OF_MOTOR]; // TOFF_MIN
extern uint8_t
    overCurrentThreshold[NUM_OF_MOTOR], // OCD
    microStepMode[NUM_OF_MOTOR]; // STEP_MODE
extern uint16_t slewRate[NUM_OF_MOTOR]; // GATECFG1
extern uint8_t slewRateNum[NUM_OF_MOTOR]; // [0]114, [1]220, [2]400, [3]520, [4]790, [5]980.
extern float lowSpeedOptimize[NUM_OF_MOTOR];
extern bool electromagnetBrakeEnable[NUM_OF_MOTOR];
extern uint16_t brakeTransitionDuration[NUM_OF_MOTOR];
extern float
    acc[NUM_OF_MOTOR],
    dec[NUM_OF_MOTOR],
    maxSpeed[NUM_OF_MOTOR],
    fullStepSpeed[NUM_OF_MOTOR];

// Servo mode
extern int32_t targetPosition[NUM_OF_MOTOR];
extern float kP[NUM_OF_MOTOR], kI[NUM_OF_MOTOR], kD[NUM_OF_MOTOR];
extern boolean isServoMode[NUM_OF_MOTOR];
#endif

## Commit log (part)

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2020-12-18 Added hardware design files.
2020-12-18 updated .gitignore
2020-12-20 Added BOM lists
2021-01-23 Added a hardware inspection sketch
2021-01-25 Added config tool files
2021-01-26 Convert multiple .ino files style to .h .cpp style
2021-01-27 Added the PlatformIO working folder
2021-02-15 update osc float/int compatibility for each commands
2021-02-17 electromagnet brake update
2021-02-18 update config tool
2021-02-25 homing functions
2021-02-26 Homing updates
2021-02-26 added new items to the configTool index.html
2021-02-26 updated main.js in configTools
2021-02-26 updated new config items
2021-03-01 update config and error
2021-03-01 MAC address update
2021-03-02 updates for diagnosis
2021-03-03 Added inServboMode error
2021-03-03 Update Arduino sketch folder
2021-03-03 Added schematics PDFs
2021-03-05 added /getHiZ
2021-03-09 Added prototype version PCB support
2021-03-09 Arduino sketch folder update
2021-03-12 Fixed setTval bug
2021-03-12 Fixed a bug at setTval
2021-03-14 configTool updates
2021-03-15 error message updates
2021-03-24 Added config json files
2021-03-24 config value fixed
2021-03-24 Added config files
2021-03-25 Added new config examples
2021-03-25 Added 23HS5628 configs
2021-04-10 Fixed a problem of starting up with a current mode.
    Fixed a problem that a request to start in a current drive mode in the configTool is ignored.
    Also fixed some typos.
2021-04-15 Fixed driving mode setups at a startup.
2021-04-15 updated the Arduino sketch directory
2021-04-21 Update README.md
    Added the forum link.
2021-04-28 Fixed loading myIp, outPort and mac when the DIP sw changed.
2021-04-30 Added EL_POS functions
    setElPos() and getElPos.
2021-04-30 reportStall is now disabled as an default condition
2021-05-02 Fixed loading bool values from config.txt
    Now integer values can be used for bool values.
2021-05-03 Updated the Arduino sketch folder
2021-05-09 Fixed some typos in the hardware inspection sketch
2021-06-28 Update the Ponoor PowerSTEP01 Library version number.
2021-09-03 update the getElPos() response and diagnosis outputs
2021-09-08 configTools CSS updated
2021-11-22 added minSpeed functions
2021-11-22 minSpeed OSC commands update
2021-11-24 configTool update and some bugfixes for minSpeed/lowSpeedOptimization
2021-11-24 change double constants to float constants
2021-11-25 Update getLowSpeedOptimizeThreshold return value
2021-11-25 Update /getMinSpeed command
2021-12-02 added /resetDevice and remove resetDev command
2021-12-03 Added updatePositionReport commands
2021-12-03 added /getPositionList
2021-12-04 confifgTool updating (not completed yet)
2021-12-06 config tool reportPositionListInterval
2021-12-07 changed command names /enablePositionReport to /setPositionReportInterval
2021-12-08 Update setElPos arguments and bug fixes for loading config
2021-12-08 updated Arduino sketch folder
2021-12-09 Fixed the response of /getLimitSw
2022-02-13 check the homing status for motion/stop commands
2022-02-14 Arduino sketch folder sync
2022-02-14 only `/run` can interrupt a homing among motion commands.
    Other motion commands will be ignored during a homing.
2022-03-03 Fixed the incorrect `/getHomeSw` response.
2022-03-24 Added the link to the latest firmware repository.
2022-03-28 File name typo fixed step400_r1_schematics.pdf
2024-03-01 Added the LED test for hardware test firmware
    Also convert the Arduino project to the platformIO project
2024-03-03 test firmware update
2024-03-04 Fixed some alarms during the test.
2024-03-06 fixed some bugs
2024-03-07 Remove old firmware directories.
2024-03-07 BOM update for r1.0.1
